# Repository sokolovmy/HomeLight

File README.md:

# Home Light
 stm32 Home Light controller

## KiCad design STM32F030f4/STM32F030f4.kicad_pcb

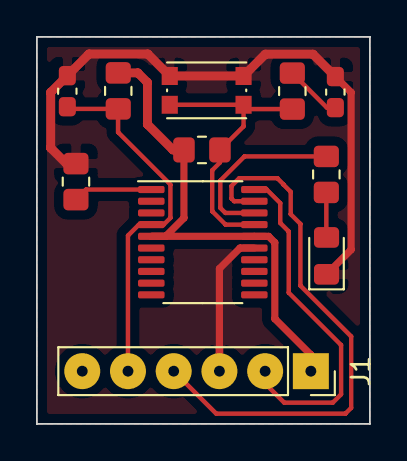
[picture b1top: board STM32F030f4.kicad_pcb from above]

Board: 2 copper layers, 18.5 x 21.5 mm, 11 parts (0 on the bottom side), 10 nets.

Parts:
C1: 100nf; C_0603_1608Metric_Pad1.08x0.95mm_HandSolder
C2: C; C_0603_1608Metric_Pad1.08x0.95mm_HandSolder
D1: LED; LED_0805_2012Metric_Pad1.15x1.40mm_HandSolder
J1: Conn_01x06_Male; PinSocket_1x06_P2.54mm_Vertical
R2, R3, R4: 100k; R_0805_2012Metric_Pad1.20x1.40mm_HandSolder
R5: 100; R_0805_2012Metric_Pad1.20x1.40mm_HandSolder
R6: 1k; R_0805_2012Metric_Pad1.20x1.40mm_HandSolder
SW1: SW_Push; SW_Push_1P1T_NO_CK_KMR2
U1: STM32F030F4Px; TSSOP-20_4.4x6.5mm_P0.65mm

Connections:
GND: C1.2, C2.1, D1.1, J1.3, R3.2, SW1.2, U1.15
NRST: C1.1, J1.5, R2.2, U1.4
unnamed: C2.2, R5.2
unnamed: D1.2, R6.1
unnamed: R3.1, U1.1
VCC: J1.1, R2.1, R4.1, U1.5, U1.16
btn: R4.2, R5.1, SW1.1, U1.17
led: R6.2, U1.18
swclk: J1.2, U1.20
swdio: J1.4, U1.19

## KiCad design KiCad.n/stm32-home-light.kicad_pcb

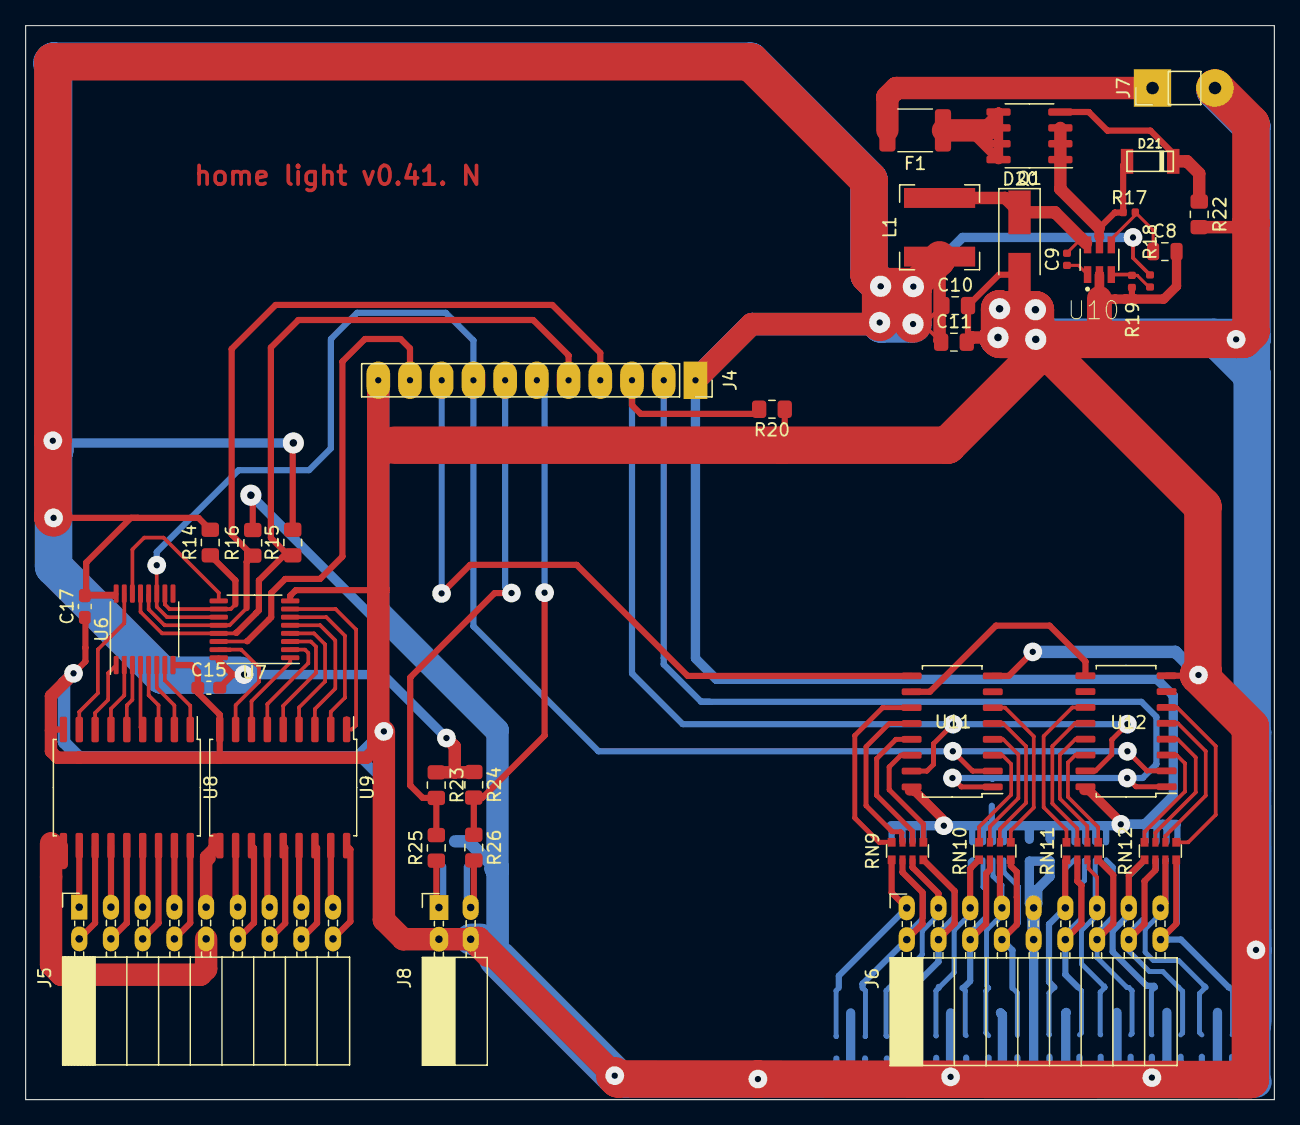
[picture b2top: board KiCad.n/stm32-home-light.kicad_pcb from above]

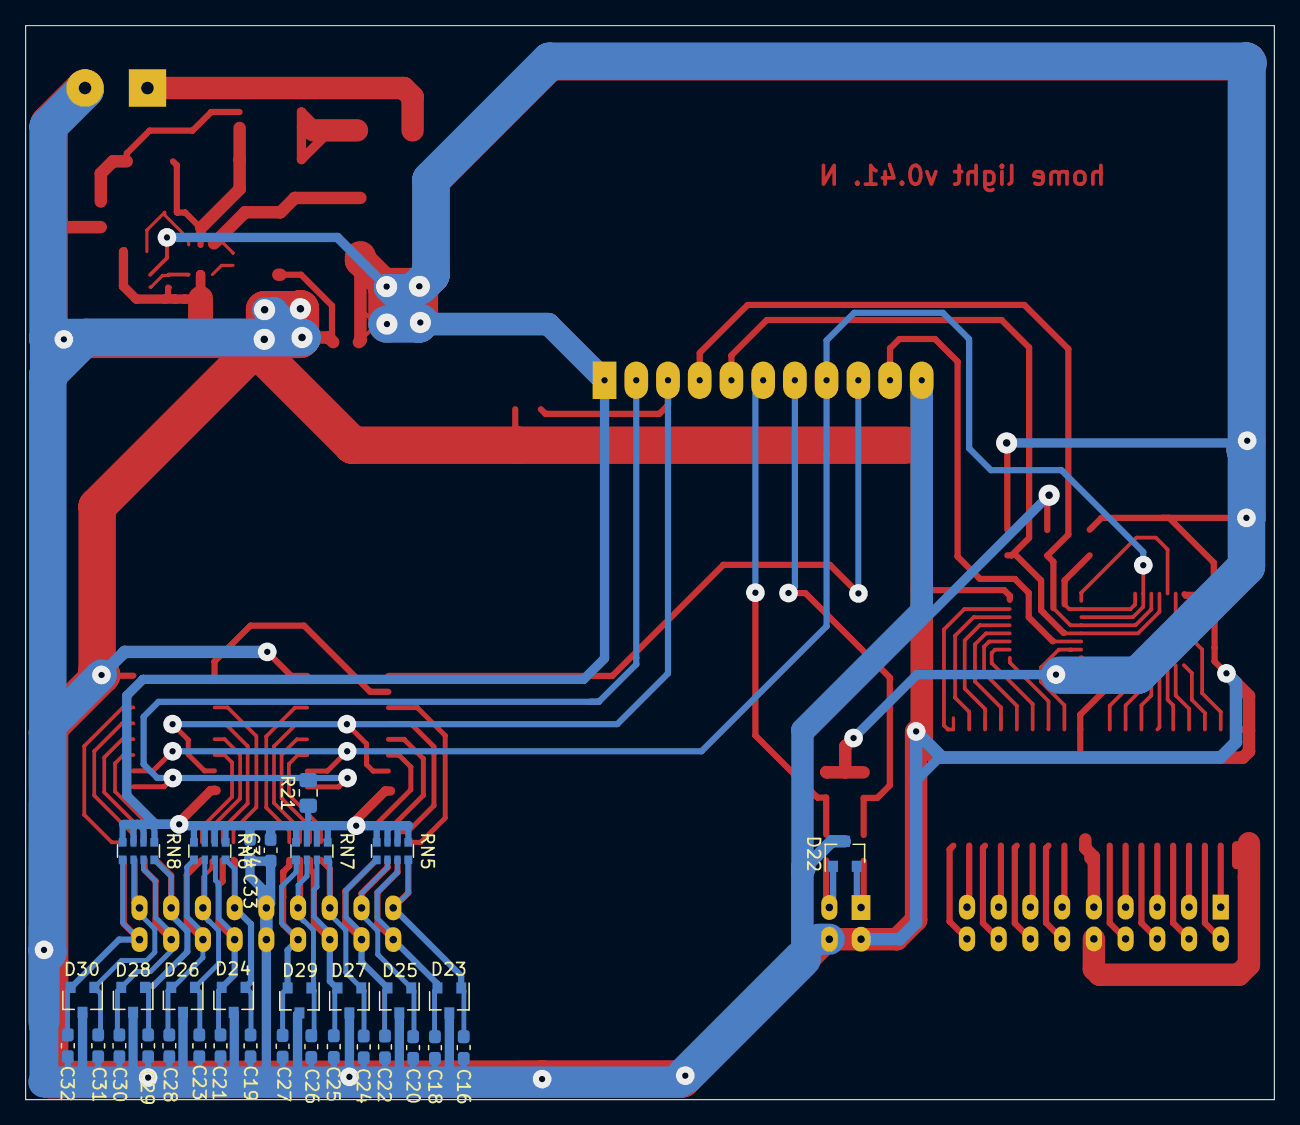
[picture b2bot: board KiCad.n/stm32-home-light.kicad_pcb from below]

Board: 2 copper layers, 100.0 x 86.0 mm, 71 parts (32 on the bottom side), 90 nets.

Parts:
C8: 10uf; C_0805_2012Metric
C9: 22nf; C_0402_1005Metric
C10: 0.1uf; C_0805_2012Metric_Pad1.15x1.40mm_HandSolder
C11: 22uf; C_0805_2012Metric_Pad1.15x1.40mm_HandSolder
C15, C16, C17, C19, C20, C23, C24, C26, C29, C31, C33, C34: 0,1; C_0603_1608Metric_Pad1.05x0.95mm_HandSolder
C18, C21, C22, C25, C27, C28, C30, C32: 0.1; C_0603_1608Metric_Pad1.05x0.95mm_HandSolder
D20: SS14; D_SMA_Handsoldering
D21: BZV55-C10; sod80c
D22, D23, D24, D25, D26, D27, D28, D29, D30: PESD3v3S2UT; SOT-23
F1: 0.1A; Fuse_1812_4532Metric_Pad1.30x3.40mm_HandSolder
J4: Crossboard2; PinSocket_1x11_P2.54mm_Vertical
J5: OUT_PORTs; PinSocket_2x09_P2.54mm_Horizontal
J6: IN_Ports; PinSocket_2x09_P2.54mm_Horizontal
J7: Power; PinHeader_1x02_P2.54mm_Vertical
J8: I2C; PinSocket_2x02_P2.54mm_Horizontal
L1: L; L_Bourns-SRN6028
Q1: AO4407A; SOIC-8_3.9x4.9mm_P1.27mm
R14, R15, R16, R20, R21, R22: 100k; R_0805_2012Metric_Pad1.15x1.40mm_HandSolder
R17: 100k; R_0402_1005Metric
R18: 3.74k; R_0402_1005Metric
R19: 1.21k; R_0402_1005Metric
R23, R24: 10k; R_0805_2012Metric_Pad1.15x1.40mm_HandSolder
R25, R26: 22; R_0805_2012Metric_Pad1.15x1.40mm_HandSolder
RN5, RN6, RN7, RN8: 10k; R_Array_Convex_4x0612_reverse
RN9, RN10, RN11, RN12: 1k; R_Array_Convex_4x0612
U6, U7: 74HC595; TSSOP-16_4.4x5mm_P0.65mm
U8, U9: ULN2803A; SOIC-18W_7.5x11.6mm_P1.27mm
U10: AP5100; SOT26
U11, U12: 74HC165; SOIC-16_4.55x10.3mm_P1.27mm

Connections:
/Sheet5F465A39/o1: U6.15, U8.8
/Sheet5F465A39/o2: U6.1, U8.7
/Sheet5F465A39/o3: U6.2, U8.6
/Sheet5F465A39/o4: U6.3, U8.5
/Sheet5F465A39/o5: U6.4, U8.4
/Sheet5F465A39/o6: U6.5, U8.3
/Sheet5F465A39/o7: U6.6, U8.2
/Sheet5F465A39/o8: U6.7, U8.1
/Sheet5F465A39/o9: U7.15, U9.8
/Sheet5F465A39/o10: U7.1, U9.7
/Sheet5F465A39/o11: U7.2, U9.6
/Sheet5F465A39/o12: U7.3, U9.5
/Sheet5F465A39/o13: U7.4, U9.4
/Sheet5F465A39/o14: U7.5, U9.3
/Sheet5F465A39/o15: U7.6, U9.2
/Sheet5F465A39/o16: U7.7, U9.1
/Sheet5F465A39/oa1: J5.1, U8.11
/Sheet5F465A39/oa2: J5.2, U8.12
/Sheet5F465A39/oa3: J5.3, U8.13
/Sheet5F465A39/oa4: J5.4, U8.14
/Sheet5F465A39/oa5: J5.5, U8.15
/Sheet5F465A39/oa6: J5.6, U8.16
/Sheet5F465A39/oa7: J5.7, U8.17
/Sheet5F465A39/oa8: J5.8, U8.18
/Sheet5F465A39/oa9: J5.11, U9.11
/Sheet5F465A39/oa10: J5.12, U9.12
/Sheet5F465A39/oa11: J5.13, U9.13
/Sheet5F465A39/oa12: J5.14, U9.14
/Sheet5F465A39/oa13: J5.15, U9.15
/Sheet5F465A39/oa14: J5.16, U9.16
/Sheet5F465A39/oa15: J5.17, U9.17
/Sheet5F465A39/oa16: J5.18, U9.18
/Sheet5F465A39/oac1: J5.10, U8.10
/Sheet5F465A39/oac2: J5.9, U9.10
GND: C8.2, C10.2, C11.2, C15.1, C16.2, C17.1, C18.2, C19.2, C20.2, C21.2, C22.2, C23.2, C24.2, C25.2, C26.2, C27.2, C28.2, C29.2, C30.2, C31.2, C32.2, C33.1, C34.1, D20.2, D22.3, D23.3, D24.3, D25.3, D26.3, D27.3, D28.3, D29.3, D30.3, J4.11, J6.9, J6.10, J7.2, J8.2, J8.4, R16.2, R19.2, R20.1, R22.2, U6.8, U7.8, U8.9, U9.9, U10.2, U11.8, U12.8
I2C2_SCL: J4.6, R24.2, R26.1
I2C2_SDA: J4.7, R23.2, R25.2
IN_CLK: J4.8, U6.11, U7.11, U11.2, U12.2
IN_CLK_Inhibit: J4.3, R20.2, U11.15, U12.15
IN_SER: J4.9, U11.9
IN_Shift_Load: J4.2, R21.2, U11.1, U12.1
LED_Ser: J4.10, U7.14
unnamed: C8.1, R17.2, U10.4
unnamed: C9.1, U10.1
unnamed: C9.2, D20.1, L1.1, U10.6
unnamed: C16.1, D23.1, J6.1, RN5.5, RN9.1
unnamed: C18.1, D23.2, J6.2, RN5.6, RN9.2
unnamed: C19.1, D24.1, J6.11, RN6.5, RN11.1
unnamed: C20.1, D25.1, J6.3, RN5.7, RN9.3
unnamed: C21.1, D24.2, J6.12, RN6.6, RN11.2
unnamed: C22.1, D25.2, J6.4, RN5.8, RN9.4
unnamed: C23.1, D26.1, J6.13, RN6.7, RN11.3
unnamed: C24.1, D27.1, J6.5, RN7.5, RN10.1
unnamed: C25.1, D27.2, J6.6, RN7.6, RN10.2
unnamed: C26.1, D29.1, J6.7, RN7.7, RN10.3
unnamed: C27.1, D29.2, J6.8, RN7.8, RN10.4
unnamed: C28.1, D26.2, J6.14, RN6.8, RN11.4
unnamed: C29.1, D28.1, J6.15, RN8.5, RN12.1
unnamed: C30.1, D28.2, J6.16, RN8.6, RN12.2
unnamed: C31.1, D30.1, J6.17, RN8.7, RN12.3
unnamed: C32.1, D30.2, J6.18, RN8.8, RN12.4
unnamed: D21.1, Q1.1, Q1.2, Q1.3, R17.1, U10.5
unnamed: D21.2, Q1.4, R22.1
unnamed: D22.1, J8.3, R26.2
unnamed: D22.2, J8.1, R25.1
unnamed: F1.1, Q1.5, Q1.6, Q1.7, Q1.8
unnamed: F1.2, J7.1
unnamed: R14.1, U6.10, U7.10
unnamed: R18.2, R19.1, U10.3
unnamed: RN9.5, U11.14
unnamed: RN9.6, U11.13
unnamed: RN9.7, U11.12
unnamed: RN9.8, U11.11
unnamed: RN10.5, U11.6
unnamed: RN10.6, U11.5
unnamed: RN10.7, U11.4
unnamed: RN10.8, U11.3
unnamed: RN11.5, U12.14
unnamed: RN11.6, U12.13
unnamed: RN11.7, U12.12
unnamed: RN11.8, U12.11
unnamed: RN12.5, U12.6
unnamed: RN12.6, U12.5
unnamed: RN12.7, U12.4
unnamed: RN12.8, U12.3
unnamed: U6.14, U7.9
unnamed: U11.10, U12.9
OUT_Enable: J4.5, R15.1, U6.13, U7.13
OUT_Push_Data: J4.4, R16.1, U6.12, U7.12
VCC: C10.1, C11.1, C15.2, C17.2, C33.2, C34.2, J4.1, L1.2, R14.2, R15.2, R18.1, R21.1, R23.1, R24.1, RN5.1, RN5.2, RN5.3, RN5.4, RN6.1, RN6.2, RN6.3, RN6.4, RN7.1, RN7.2, RN7.3, RN7.4, RN8.1, RN8.2, RN8.3, RN8.4, U6.16, U7.16, U11.16, U12.16

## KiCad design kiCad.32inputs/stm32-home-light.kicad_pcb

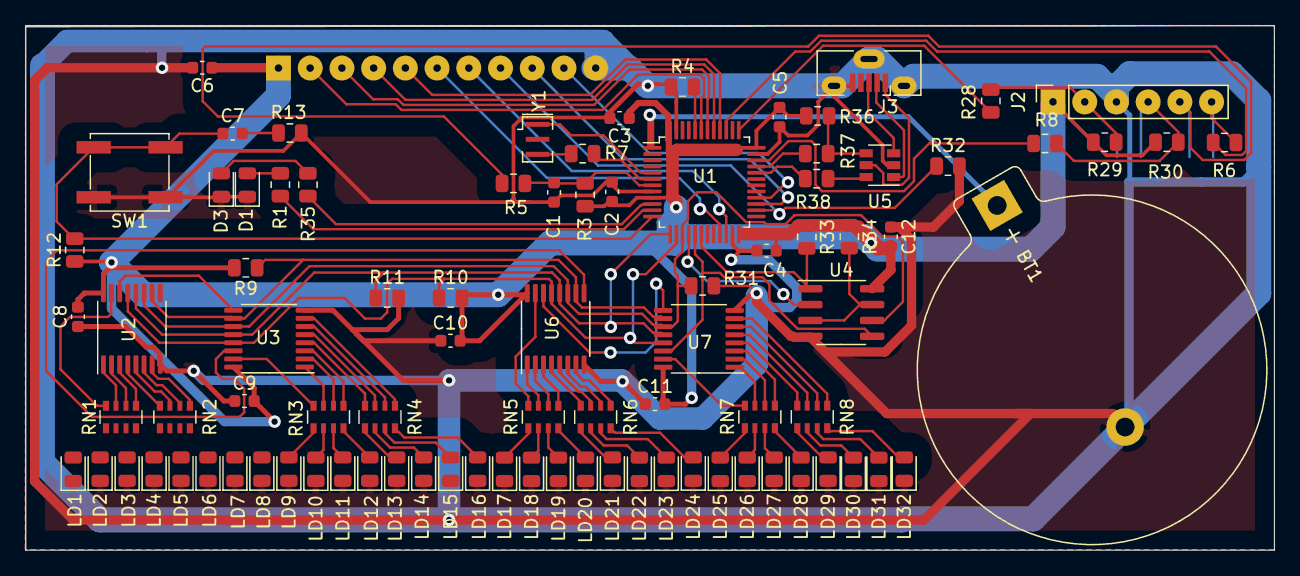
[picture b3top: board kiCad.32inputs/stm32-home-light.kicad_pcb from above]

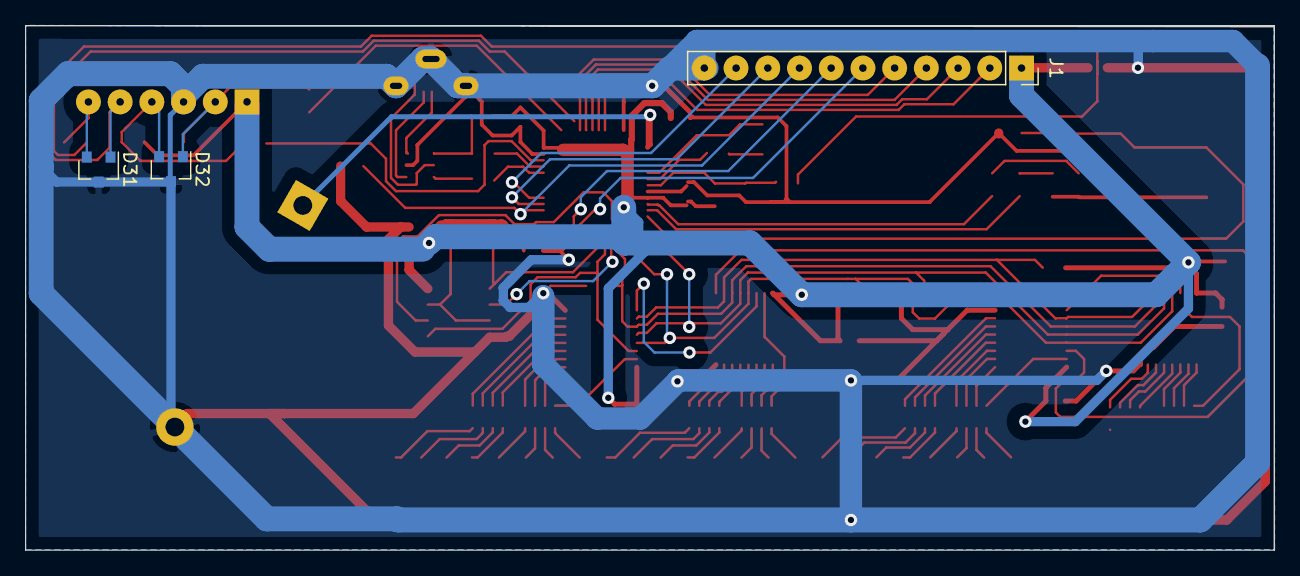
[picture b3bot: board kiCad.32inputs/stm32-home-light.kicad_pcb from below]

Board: 2 copper layers, 100.0 x 42.0 mm, 92 parts (3 on the bottom side), 112 nets.

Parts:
BT1: 3v; BatteryHolder_Keystone_106_1x20mm
C1, C2, C3, C4, C5: 0.1uf; C_0603_1608Metric
C6: 1uf; C_0603_1608Metric
C7: 100nf; C_0603_1608Metric
C8, C9, C10, C11, C12: 0,1; C_0603_1608Metric
D1, D3: PESD3V3L4UG; LED_0805_2012Metric
D31, D32: PESD3v3S2UT; SOT-23
J1: Crossboard; PinSocket_1x11_P2.54mm_Vertical
J2: Program; PinSocket_1x06_P2.54mm_Vertical
J3: USB_B_Micro; USB_Micro-B_Molex-105133-0001
LD1: LD1; LED_0805_2012Metric
LD2: LD2; LED_0805_2012Metric
LD3: LD3; LED_0805_2012Metric
LD4: LD4; LED_0805_2012Metric
LD5: LD5; LED_0805_2012Metric
LD6: LD6; LED_0805_2012Metric
LD7: LD7; LED_0805_2012Metric
LD8: LD8; LED_0805_2012Metric
LD9: LD9; LED_0805_2012Metric
LD10: LD10; LED_0805_2012Metric
LD11: LD11; LED_0805_2012Metric
LD12: LD12; LED_0805_2012Metric
LD13: LD13; LED_0805_2012Metric
LD14: LD14; LED_0805_2012Metric
LD15: LD15; LED_0805_2012Metric
LD16: LD16; LED_0805_2012Metric
LD17: LD17; LED_0805_2012Metric
LD18: LD18; LED_0805_2012Metric
LD19: LD19; LED_0805_2012Metric
LD20: LD20; LED_0805_2012Metric
LD21: LD21; LED_0805_2012Metric
LD22: LD22; LED_0805_2012Metric
LD23: LD23; LED_0805_2012Metric
LD24: LD24; LED_0805_2012Metric
LD25: LD25; LED_0805_2012Metric
LD26: LD26; LED_0805_2012Metric
LD27: LD27; LED_0805_2012Metric
LD28: LD28; LED_0805_2012Metric
LD29: LD29; LED_0805_2012Metric
LD30: LD30; LED_0805_2012Metric
LD31: LD31; LED_0805_2012Metric
LD32: LD32; LED_0805_2012Metric
R1, R7, R35: 1k; R_0805_2012Metric
R3, R4, R9, R10, R11, R12, R29, R30, R31, R32, R33, R34: 100k; R_0805_2012Metric
R5, R6, R8, R28, R37, R38: 22; R_0805_2012Metric
R13: 100; R_0805_2012Metric
R36: 1.5k; R_0805_2012Metric
RN1, RN2, RN3, RN4, RN5, RN6, RN7, RN8: 1k; R_Array_Convex_4x0603_reverse
SW1: BTN; SW_SPST_EVPBF
U1: STM32F103C8Tx; LQFP-48_7x7mm_P0.5mm
U2, U3, U6, U7: 74HC595; TSSOP-16_4.4x5mm_P0.65mm
U4: M95256-WMN6P; SOIC-8_3.9x4.9mm_P1.27mm
U5: USBLC6-2SC6; SOT-23-6
Y1: 8mhz; Resonator_SMD_muRata_CSTxExxV-3Pin_3.0x1.1mm

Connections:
BTN: C7.1, R12.2, SW1.2, U1.12
EEPROM_SELECT: R33.2, U1.18, U4.1
GND: BT1.2, C1.2, C2.2, C3.2, C4.2, C5.2, C6.2, C8.1, C9.1, C10.1, C11.1, C12.1, D1.1, D3.1, D31.3, D32.3, J1.11, J2.3, J3.5, J3.6, LD1.1, LD2.1, LD3.1, LD4.1, LD5.1, LD6.1, LD7.1, LD8.1, LD9.1, LD10.1, LD11.1, LD12.1, LD13.1, LD14.1, LD15.1, LD16.1, LD17.1, LD18.1, LD19.1, LD20.1, LD21.1, LD22.1, LD23.1, LD24.1, LD25.1, LD26.1, LD27.1, LD28.1, LD29.1, LD30.1, LD31.1, LD32.1, R4.1, R11.2, R13.1, R31.2, R32.2, SW1.1, U1.8, U1.23, U1.35, U1.47, U2.8, U3.8, U4.4, U5.2, U6.8, U7.8, Y1.2
I2C2_SCL: J1.6, U1.21
I2C2_SDA: J1.7, U1.22
IN_CLK_Inhibit: J1.3, U1.42
IN_Shift_Load: J1.2, U1.43
LED_CLK: R31.1, U1.15, U2.11, U3.11, U4.6, U6.11, U7.11
LED_Enable: R10.1, U1.14, U2.13, U3.13, U6.13, U7.13
LED_GREEN: R35.1, U1.10
LED_Push_Data: R11.1, U1.13, U2.12, U3.12, U6.12, U7.12
LED_RED: R1.1, U1.11
LED_Ser: U1.17, U4.5, U7.14
NRST: D31.1, J2.5, R5.1
unnamed: BT1.1, U1.1
unnamed: C1.1, R3.1, R5.2, U1.7
unnamed: C7.2, R13.2
unnamed: D1.2, R1.2
unnamed: D3.2, R35.2
unnamed: J3.1, U5.5
unnamed: J3.2, U5.1
unnamed: J3.3, U5.3
unnamed: LD1.2, RN1.8
unnamed: LD2.2, RN1.7
unnamed: LD3.2, RN1.6
unnamed: LD4.2, RN1.5
unnamed: LD5.2, RN2.8
unnamed: LD6.2, RN2.7
unnamed: LD7.2, RN2.6
unnamed: LD8.2, RN2.5
unnamed: LD9.2, RN3.8
unnamed: LD10.2, RN3.7
unnamed: LD11.2, RN3.6
unnamed: LD12.2, RN3.5
unnamed: LD13.2, RN4.8
unnamed: LD14.2, RN4.7
unnamed: LD15.2, RN4.6
unnamed: LD16.2, RN4.5
unnamed: LD17.2, RN5.8
unnamed: LD18.2, RN5.7
unnamed: LD19.2, RN5.6
unnamed: LD20.2, RN5.5
unnamed: LD21.2, RN6.8
unnamed: LD22.2, RN6.7
unnamed: LD23.2, RN6.6
unnamed: LD24.2, RN6.5
unnamed: LD25.2, RN7.8
unnamed: LD26.2, RN7.7
unnamed: LD27.2, RN7.6
unnamed: LD28.2, RN7.5
unnamed: LD29.2, RN8.8
unnamed: LD30.2, RN8.7
unnamed: LD31.2, RN8.6
unnamed: LD32.2, RN8.5
unnamed: R4.2, U1.44
unnamed: R6.1, U1.39
unnamed: R7.1, Y1.3
unnamed: R7.2, U1.6
unnamed: R8.1, U1.34
unnamed: R9.1, U2.10, U3.10, U6.10, U7.10
unnamed: R28.1, U1.37
unnamed: R34.2, U4.3, U4.7
unnamed: R36.1, R37.2, U5.4
unnamed: R38.2, U5.6
unnamed: RN1.1, U2.15
unnamed: RN1.2, U2.1
unnamed: RN1.3, U2.2
unnamed: RN1.4, U2.3
unnamed: RN2.1, U2.4
unnamed: RN2.2, U2.5
unnamed: RN2.3, U2.6
unnamed: RN2.4, U2.7
unnamed: RN3.1, U3.15
unnamed: RN3.2, U3.1
unnamed: RN3.3, U3.2
unnamed: RN3.4, U3.3
unnamed: RN4.1, U3.4
unnamed: RN4.2, U3.5
unnamed: RN4.3, U3.6
unnamed: RN4.4, U3.7
unnamed: RN5.1, U6.15
unnamed: RN5.2, U6.1
unnamed: RN5.3, U6.2
unnamed: RN5.4, U6.3
unnamed: RN6.1, U6.4
unnamed: RN6.2, U6.5
unnamed: RN6.3, U6.6
unnamed: RN6.4, U6.7
unnamed: RN7.1, U7.15
unnamed: RN7.2, U7.1
unnamed: RN7.3, U7.2
unnamed: RN7.4, U7.3
unnamed: RN8.1, U7.4
unnamed: RN8.2, U7.5
unnamed: RN8.3, U7.6
unnamed: RN8.4, U7.7
unnamed: U1.5, Y1.1
unnamed: U2.14, U3.9
unnamed: U3.14, U6.9
unnamed: U6.14, U7.9
OUT_Enable: J1.5, U1.40
OUT_Push_Data: J1.4, U1.41
SPI1_MISO: U1.16, U4.2
SPI2_CLK: J1.8, R32.1, U1.26
SPI2_MISO: J1.9, U1.27
SPI2_MOSI: J1.10, U1.28
SWCLK: D32.1, J2.2, R28.2, R29.2
SWDIO: D32.2, J2.4, R8.2, R30.2
SWO: D31.2, J2.6, R6.2
USB+: R37.1, U1.33
USB-: R38.1, U1.32
VCC: C2.1, C3.1, C4.1, C5.1, C6.1, C8.2, C9.2, C10.2, C11.2, C12.2, J1.1, J2.1, R3.2, R9.2, R10.2, R12.1, R29.1, R30.1, R33.1, R34.1, R36.2, U1.9, U1.24, U1.36, U1.48, U2.16, U3.16, U4.8, U6.16, U7.16

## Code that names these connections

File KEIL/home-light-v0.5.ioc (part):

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Mcu.Name=STM32F103C(8-B)Tx
Mcu.Package=LQFP48
Mcu.UserName=STM32F103C8Tx
PA1.GPIOParameters=GPIO_Label
PA1.GPIO_Label=IN_LOAD
PA1.Signal=GPIO_Output
PA10.GPIOParameters=GPIO_Label
PA10.GPIO_Label=LED_RED
PA10.Signal=GPIO_Output
PA11.Mode=Device
PA11.Signal=USB_DM
PA12.Mode=Device
PA12.Signal=USB_DP
PA13.Mode=Serial_Wire
PA13.Signal=SYS_JTMS-SWDIO
PA14.Mode=Serial_Wire
PA14.Signal=SYS_JTCK-SWCLK
PA15.GPIOParameters=GPIO_Label
PA15.GPIO_Label=BTN
PA15.Signal=GPIO_Input
PA2.GPIOParameters=GPIO_Label
PA2.GPIO_Label=IN_INHB
PA2.Signal=GPIO_Output
PA3.GPIOParameters=PinState,GPIO_Label
PA3.GPIO_Label=OUT_ENABLE
PA3.PinState=GPIO_PIN_SET
PA3.Signal=GPIO_Output
PA4.GPIOParameters=GPIO_Label
PA4.GPIO_Label=OUT_PUSH_DATA
PA4.Signal=GPIO_Output
PA5.Mode=Full_Duplex_Master
PA5.Signal=SPI1_SCK
PA6.Mode=Full_Duplex_Master
PA6.Signal=SPI1_MISO
PA7.Mode=Full_Duplex_Master
PA7.Signal=SPI1_MOSI
PA8.GPIOParameters=GPIO_Label
PA8.GPIO_Label=LED_GREEN
PA8.Signal=GPIO_Output
PA9.GPIOParameters=GPIO_Label
PA9.GPIO_Label=LED_YELLOW
PA9.Signal=GPIO_Output
PB0.GPIOParameters=GPIO_Speed,PinState,GPIO_Label
PB0.GPIO_Label=EEPROM_CS
PB0.GPIO_Speed=GPIO_SPEED_FREQ_LOW
PB0.PinState=GPIO_PIN_SET
PB0.Signal=GPIO_Output
PB13.Mode=Full_Duplex_Master
PB13.Signal=SPI2_SCK
PB14.Mode=Full_Duplex_Master
PB14.Signal=SPI2_MISO
PB15.Mode=Full_Duplex_Master
PB15.Signal=SPI2_MOSI
PB4.GPIOParameters=GPIO_Label
PB4.GPIO_Label=LED_PUSH_DATA
PB4.Signal=GPIO_Output
PB5.GPIOParameters=PinState,GPIO_Label
PB5.GPIO_Label=LED_ENABLE
PB5.PinState=GPIO_PIN_SET
PB5.Signal=GPIO_Output
PD0-OSC_IN.Mode=HSE-External-Oscillator
PD0-OSC_IN.Signal=RCC_OSC_IN
PD1-OSC_OUT.Mode=HSE-External-Oscillator
PD1-OSC_OUT.Signal=RCC_OSC_OUT
RCC.SYSCLKFreq_VALUE=72000000
RCC.SYSCLKSource=RCC_SYSCLKSOURCE_PLLCLK
board=custom
